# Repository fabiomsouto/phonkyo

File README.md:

# Phonkyo

A PiHat for Onkyo RI-enabled devices, hence the name (PiHat Onkyo).

Phonkyo makes a Raspberry Pi behave like one of Onkyo's own docks. Onkyo receivers have a small RI (Remote
Interactive) jack on the back, which docks use to switch the receiver on and change it to the dock input. Phonkyo speaks
the same protocol, so when you start playing music the receiver comes on and selects DOCK by itself, and after a few
minutes of silence it switches off again.

The music comes from the Pi itself: a PCM5102A DAC on the hat turns it into an AirPlay 2 receiver, a Spotify Connect
device and a headless Plexamp player, feeding the receiver's dock input through a line-level output.

I believe this device could also be used for other RI-enabled devices, such as Marantz, but I have no way to test it
(and therefore implement support)!

## What it does

- **Follows playback.** When something starts playing, the receiver powers on and switches to its DOCK input. When
  playback stops, it switches off again, but only if phonkyo was the one that turned it on.
- **High-quality line output.** PCM5102A DAC, 24-bit/192 kHz, on a 3.5 mm line-out jack meant for an amplifier's
  line input.
- **Onkyo RI control.** A second 3.5 mm jack connects to the receiver's RI port. It sends commands and listens to the
  codes the receiver sends back.
- **The receiver's remote controls Plexamp.** Play/pause, next, previous, fast-forward, rewind and repeat on the
  receiver's own remote work on Plexamp, just as they would on an Onkyo dock. AirPlay and Spotify can't be controlled
  this way; see `install/MANIFEST.md`.
- **Plug-and-play (v0.3).** A HAT ID EEPROM lets the Raspberry Pi recognise the board and load the sound card by itself,
  so there is nothing to add to `config.txt`.

Tested with an Onkyo TX-8020 and a Raspberry Pi Zero 2 W. Selecting the TV input and changing the volume are not
possible over RI on the TX-8020; `install/MANIFEST.md` records the full code search.

## Hardware

| | |
|---|---|
| Form factor | pHAT, 65 x 30 mm, for the Raspberry Pi Zero 2 W (fits any 40-pin Pi) |
| DAC | TI PCM5102A over I2S, own 3.3 V analog regulator |
| Outputs | 3.5 mm line out (J2), 3.5 mm Onkyo RI (J4) |
| RI line | GPIO25, with a series resistor and ESD clamp from v0.3 |
| ID EEPROM | CAT24C256 on ID_SD/ID_SC, write protect by solder jumper (v0.3) |

| Top | Bottom |
|---|---|
|  |  |

The design is in KiCad 10: `phonkyo.kicad_sch` and `phonkyo.kicad_pcb`. **v0.2 is the latest revision that has been built
and tested; v0.3 is designed but not yet built.**

## Buying one

Phonkyo is sold in small, hand-built batches through [obcecado.com/phonkyo](https://obcecado.com/phonkyo/).

- **Basic kit:** an assembled Phonkyo board with the 40-pin header already soldered. €30 plus shipping at the time
  of writing; the product page has the current price.
- **Complete kit:** also includes an audio cable, an RI cable and a 3D-printed case. Not available yet.
- **Shipping** is to European Union countries only.

To order, email [phonkyo@obcecado.com](mailto:phonkyo@obcecado.com?subject=Phonkyo%20order) with:

- the kit you want and how many
- the country it ships to
- your receiver model

I'll reply with the total including shipping and how to pay. There's no online checkout.

RI support varies from receiver to receiver, so check the
[compatibility table](https://obcecado.com/phonkyo/#receiver-compatibility) before ordering. Only the Onkyo TX-8020 has
been tested so far. If yours isn't listed, mention it in your email and I'll tell you what I know.

## Getting started

The software runs on Raspberry Pi OS Lite 64-bit (Trixie) on a Raspberry Pi Zero 2 W. On a fresh install, connect to
the Pi over SSH and run:

```sh
curl -fsSL https://obcecado.com/phonkyo/install.sh | bash
```

It asks which players you want and what to call the device, installs everything, and reboots when it's done. It takes
about 10-15 minutes. Plexamp needs a one-time sign-in code from [plex.tv/claim](https://plex.tv/claim), which it asks
for at the right moment. Running it again is safe, and is how you update. The script is `install/phonkyo-setup.sh`.

The [setup guide](https://obcecado.com/phonkyo/setup/) covers flashing the microSD card and the steps by hand, and
`install/MANIFEST.md` is the full technical record of what gets installed and why:

- the DAC and the ALSA setup
- AirPlay 2 (shairport-sync), Spotify Connect (raspotify) and Plexamp
- the RI control code in `software/phonkyo/` and the `phonkyo-monitor` service that follows playback

## Making boards

`production/v0.3/` has everything needed to order assembled boards from JLCPCB: Gerbers, drill files, and a BOM and
placement file with LCSC part numbers. Its README covers the order settings, the parts, and a bring-up checklist for new
boards. The 40-pin header is soldered by hand, and the ID EEPROM is programmed with `make flash` in `hardware/eeprom/`.

`docs/hardware-review-v0.3.md` is a design review of v0.3: what was found, and what was changed.

## Repository layout

| Path | Contents |
|---|---|
| `phonkyo.kicad_*` | KiCad 10 schematic, PCB and project |
| `production/` | Fabrication files for each revision |
| `hardware/eeprom/` | HAT ID EEPROM image source, device tree overlay, build and flash |
| `software/` | RI control, playback monitor, RI sniffer, board detection, systemd unit |
| `install/MANIFEST.md` | Software setup, measured RI timing and verified RI codes |
| `docs/` | Hardware review |
| `art/` | Board artwork and product renders |
| `3dmodels/` | 3D models missing from the KiCad library |
| `adc/` | PCM5102A datasheet |

## Release notes

### v0.1

Initial release of the Phonkyo project. There is no ID EEPROM present yet, and all the hat exposes is a 3.5mm jack that's
connected to the GPIO pin 25 on the Raspberry Pi. Use a mono or a stereo male-to-male cable to connect your Onkyo remote control to the hat.

### v0.2

This release adds the much acclaimed PCM5102A DAC to the design, allowing to expand the functionality of the device beyond a simple
remote control for your home theater system with RI. Depending on your needs, you will now be able to:
- Control your remote interface home theater to your liking
- Expose the Raspberry Pi as a Spotify device
- Expose the Raspberry Pi as an Airplay device
- Expose the Raspberry Pi as a Plex headless player

### v0.3

This release improves on the board design, particularly around power and ground rails, and removes the SCK jumper, as I don't
predict the need for an external clock source in this particular design. It also:
- Fits the HAT ID EEPROM, so the Raspberry Pi sets the board up by itself
- Adds ESD protection and a series resistor on the RI jack
- Moves the DAC's decoupling capacitors next to its pins, and adds one on the analog supply
- Moves the I2S bit clock onto the top layer, over an unbroken ground plane

## Related projects and documentation

[Macsbug article on PCM5102A](https://macsbug-wordpress-com.translate.goog/2021/02/19/web-radio-of-m5stack-pcm5102a-i2s-dac/)

[TI PCM5102A](https://www.ti.com/lit/ds/symlink/pcm5102a.pdf)

[phatDAC](https://shop.pimoroni.com/products/phat-dac) as inspiration

## License

Phonkyo is licensed under [Creative Commons Attribution-NonCommercial-ShareAlike 4.0 International](LICENSE)
(CC BY-NC-SA 4.0). You may build, modify and share it for non-commercial purposes, as long as you credit the project
and share your changes under the same licence. For commercial use, get in touch.

### Third-party content

These files are not covered by the licence above and remain the property of their owners:

- `adc/pcm5102a.pdf`: the PCM5102A datasheet, © Texas Instruments, included unaltered.
- `3dmodels/Jack_3.5mm_PJ-320D-4A.step`: the 3D model of the Korean Hroparts PJ-320D-4A jack (LCSC C95562), from
  LCSC/EasyEDA, used for the 3D renders only.
- Footprints and symbols from the KiCad libraries, used under the KiCad libraries' licence (CC BY-SA 4.0 with an
  exception for designs that use them).

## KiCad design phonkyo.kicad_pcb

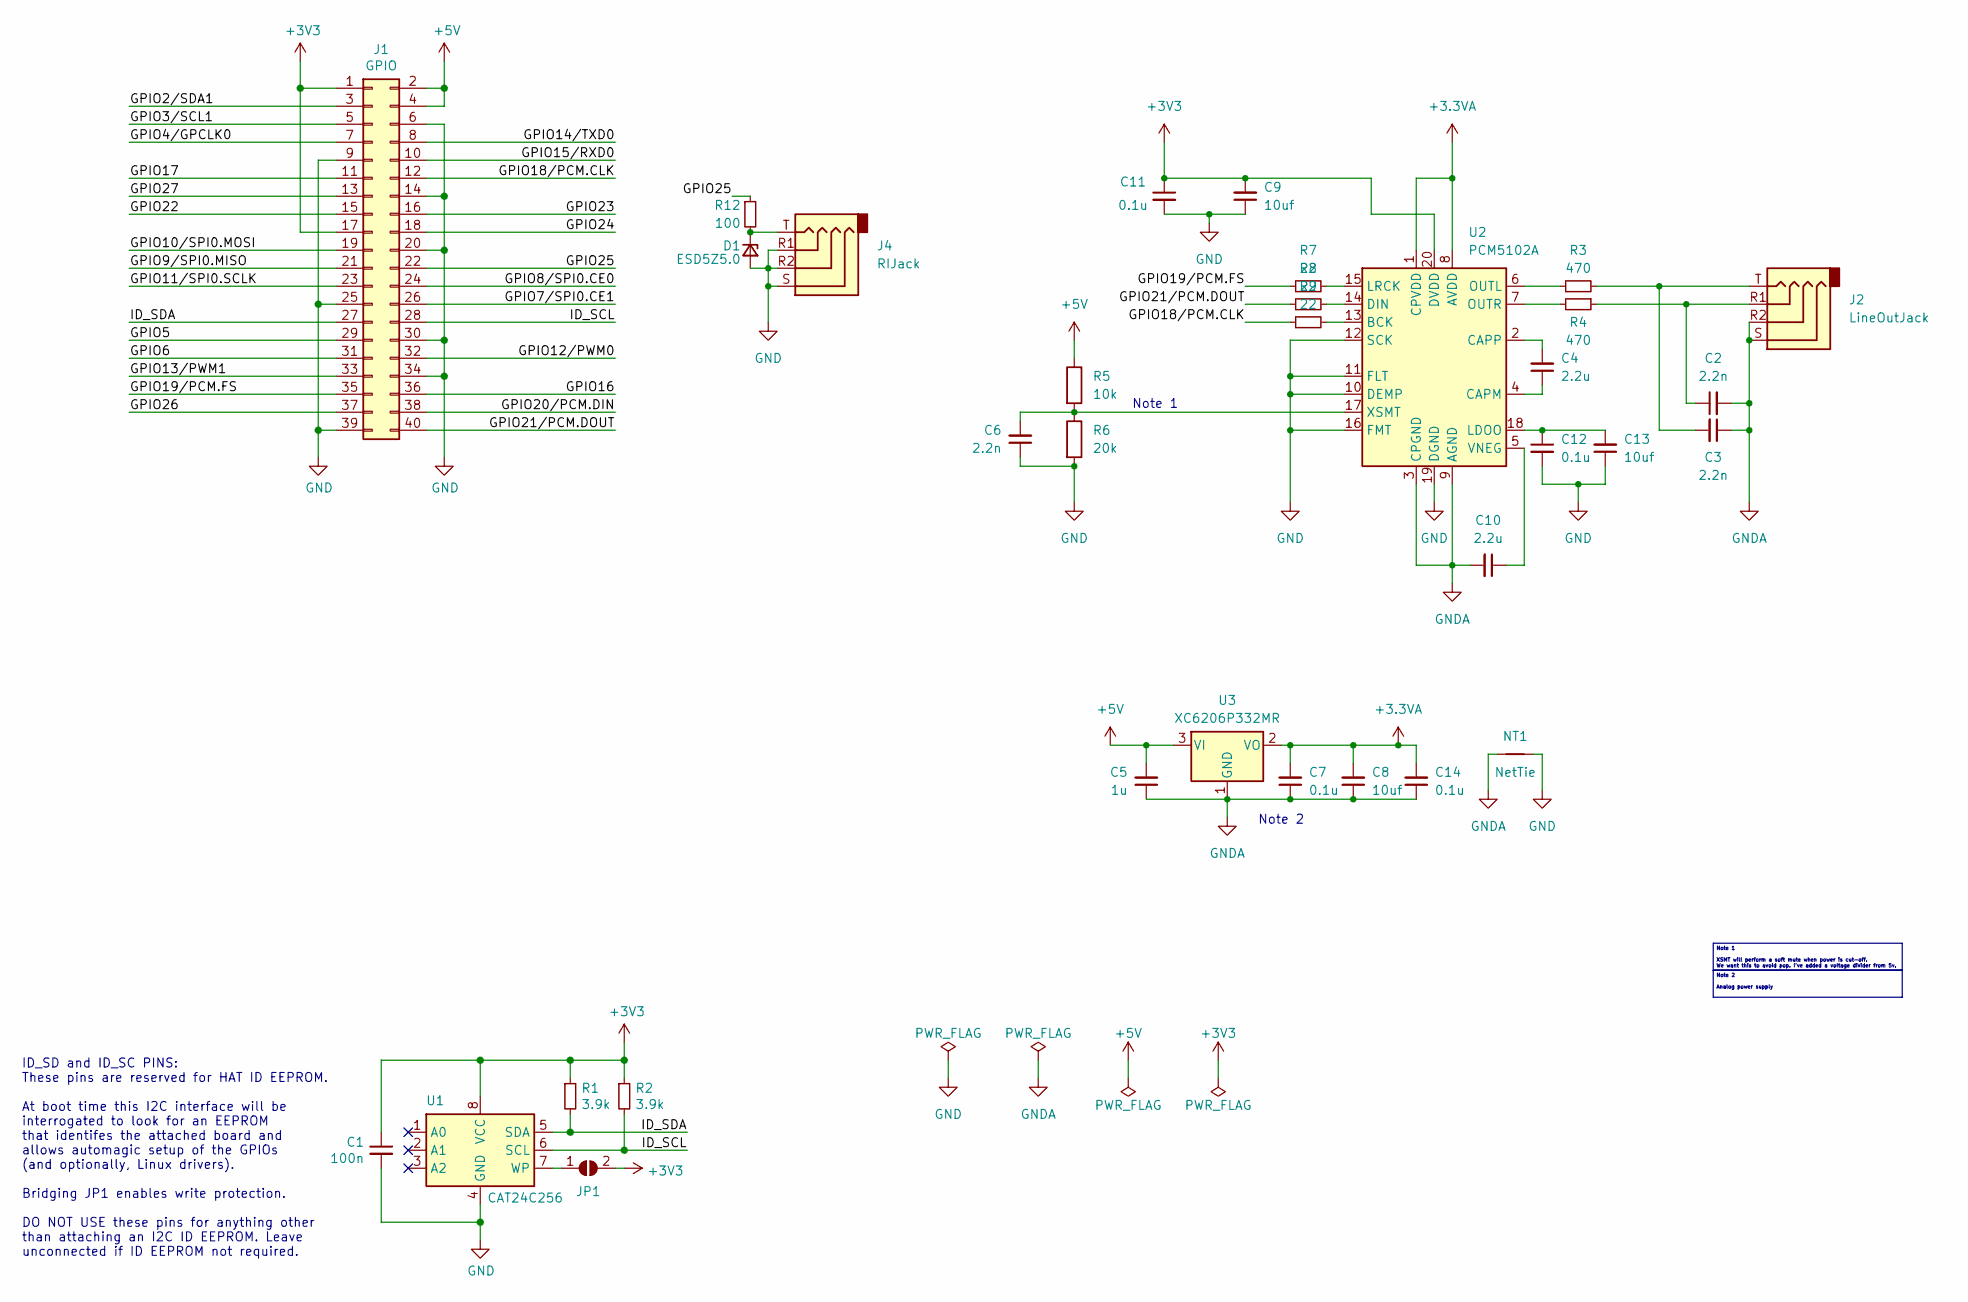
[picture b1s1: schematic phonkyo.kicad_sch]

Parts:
C1: 100n; C_0402_1005Metric; LCSC C1525
C2, C3, C6: 2.2n; C_0402_1005Metric; LCSC C385029
C4, C10: 2.2u; C_0402_1005Metric; LCSC C107369
C5: 1u; C_0603_1608Metric; LCSC C15849
C7: 0.1u; C_0603_1608Metric; LCSC C14663
C8, C9, C13: 10uf; C_0603_1608Metric; LCSC C19702
C11, C12, C14: 0.1u; C_0402_1005Metric; LCSC C1525
D1: ESD5Z5.0; D_SOD-523; LCSC C82044
J1: GPIO; PinSocket_2x20_P2.54mm_Vertical; LCSC C5124634
J2: LineOutJack; Jack_3.5mm_KoreanHropartsElec_PJ-320D-4A_Horizontal; LCSC C95562
J4: RIJack; Jack_3.5mm_KoreanHropartsElec_PJ-320D-4A_Horizontal; LCSC C95562
JP1: ID_WP; SolderJumper-2_P1.3mm_Open_Pad1.0x1.5mm
NT1: NetTie; NetTie-2_SMD_Pad0.5mm
R1, R2: 3.9k; R_0402_1005Metric; LCSC C131467
R3, R4: 470; R_0402_1005Metric; LCSC C25117
R5: 10k; R_0402_1005Metric; LCSC C25744
R6: 20k; R_0402_1005Metric; LCSC C25765
R7, R8, R9: 22; R_0402_1005Metric; LCSC C25092
R12: 100; R_0402_1005Metric; LCSC C25076
U1: CAT24C256; TSSOP-8_4.4x3mm_P0.65mm; LCSC C146734
U2: PCM5102A; TSSOP-20_4.4x6.5mm_P0.65mm; LCSC C107671
U3: XC6206P332MR; SOT-23-3; LCSC C5446

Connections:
+3.3VA: C7.2, C8.2, C14.2, U2.1 (CPVDD), U2.8 (AVDD), U3.2 (VO)
+3V3: C1.1, C9.2, C11.1, J1.1, J1.17, JP1.2 (B), R1.1, R2.1, U1.8 (VCC), U2.20 (DVDD)
+5V: C5.2, J1.2, J1.4, R5.1, U3.3 (VI)
/GPIO2/SDA1: J1.3
/GPIO3/SCL1: J1.5
/GPIO4/GPCLK0: J1.7
/GPIO5: J1.29
/GPIO6: J1.31
/GPIO7/SPI0.CE1: J1.26
/GPIO8/SPI0.CE0: J1.24
/GPIO9/SPI0.MISO: J1.21
/GPIO10/SPI0.MOSI: J1.19
/GPIO11/SPI0.SCLK: J1.23
/GPIO12/PWM0: J1.32
/GPIO13/PWM1: J1.33
/GPIO14/TXD0: J1.8
/GPIO15/RXD0: J1.10
/GPIO16: J1.36
/GPIO17: J1.11
/GPIO18/PCM.CLK: J1.12, R9.1
/GPIO19/PCM.FS: J1.35, R7.1
/GPIO20/PCM.DIN: J1.38
/GPIO21/PCM.DOUT: J1.40, R8.1
/GPIO22: J1.15
/GPIO23: J1.16
/GPIO24: J1.18
/GPIO25: J1.22, R12.1
/GPIO26: J1.37
/GPIO27: J1.13
/ID_SCL: J1.28, R2.2, U1.6 (SCL)
/ID_SDA: J1.27, R1.2, U1.5 (SDA)
GND: C1.2, C6.1, C9.1, C11.2, C12.2, C13.1, D1.2 (A), J1.6, J1.9, J1.14, J1.20, J1.25, J1.30, J1.34, J1.39, J4.R1, J4.R2, J4.S, NT1.2, R6.2, U1.4 (GND), U2.10 (DEMP), U2.11 (FLT), U2.12 (SCK), U2.16 (FMT), U2.19 (DGND)
GNDA: C2.2, C3.1, C5.1, C7.1, C8.1, C10.2, C14.1, J2.R2, J2.S, NT1.1, U2.3 (CPGND), U2.9 (AGND), U3.1 (GND)
unnamed: C2.1, J2.R1, R4.1
unnamed: C3.2, J2.T, R3.2
unnamed: D1.1 (K), J4.T, R12.2
unnamed: JP1.1 (A), U1.7 (WP)
unnamed: R9.2, U2.13 (BCK)
unnamed: C4.1, U2.4 (CAPM)
unnamed: C4.2, U2.2 (CAPP)
unnamed: R8.2, U2.14 (DIN)
unnamed: C12.1, C13.2, U2.18 (LDOO)
unnamed: R7.2, U2.15 (LRCK)
unnamed: R3.1, U2.6 (OUTL)
unnamed: R4.2, U2.7 (OUTR)
unnamed: C10.1, U2.5 (VNEG)
unnamed: C6.2, R5.2, R6.1, U2.17 (XSMT)

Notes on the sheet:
Note 2
ID_SD and ID_SC PINS: These pins are reserved for HAT ID EEPROM. At boot time this I2C interface will be interrogated to look for an EEPROM that identifes the attached board and allows automagic setup of the GPIOs (and optionally, Linux drivers). Bridging JP1 enables write protection. DO NOT USE th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
Note 1
Note 1 XSMT will perform a soft mute when power is cut-off. We want this to avoid pop. I've added a voltage divider from 5v.
Note 2 Analog power supply

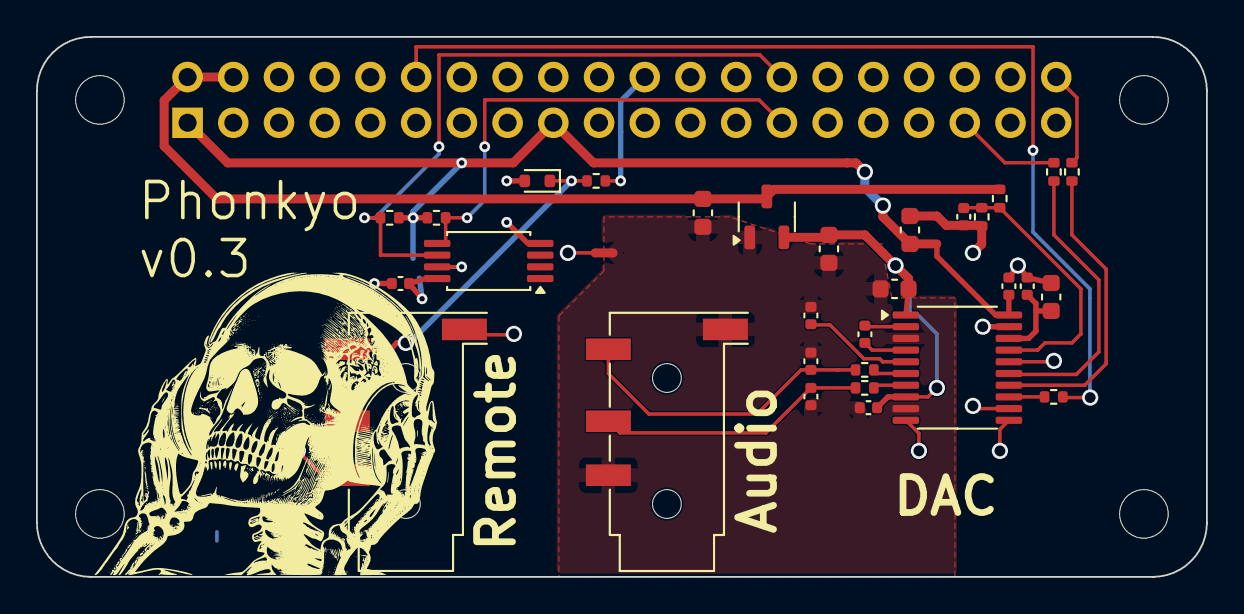
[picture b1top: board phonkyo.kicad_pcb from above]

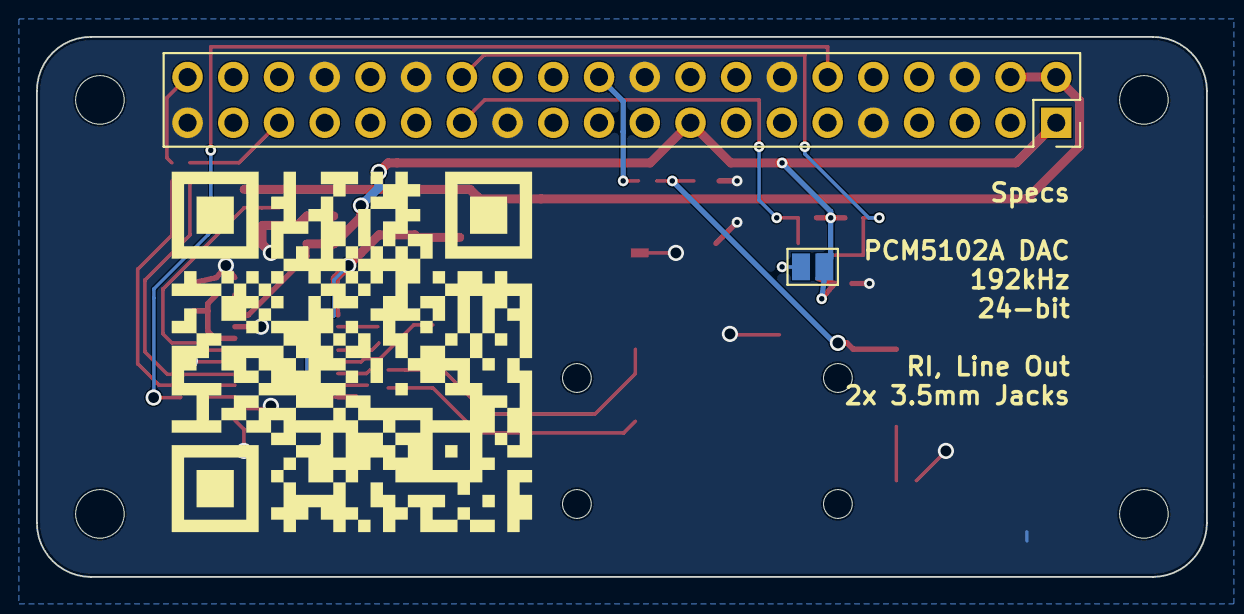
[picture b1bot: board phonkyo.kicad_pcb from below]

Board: 2 copper layers, 65.0 x 30.0 mm, 37 parts (2 on the bottom side), 25 nets.

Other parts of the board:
MH1, MH2, MH3, MH4: MountingHole_2.7mm_M2.5

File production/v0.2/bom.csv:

"Reference","Value","Datasheet","Footprint","Qty","DNP"
"C2,C3,C6","2.2n","~","Capacitor_SMD:C_0402_1005Metric","3",""
"C4,C10","2.2u","~","Capacitor_SMD:C_0402_1005Metric","2",""
"C5","1u","~","Capacitor_SMD:C_0603_1608Metric","1",""
"C7,C11,C12","0.1u","~","Capacitor_SMD:C_0603_1608Metric","3",""
"C8,C9,C13","10uf","~","Capacitor_SMD:C_0603_1608Metric","3",""
"J1","GPIO","","Connector_PinSocket_2.54mm:PinSocket_2x20_P2.54mm_Vertical","1",""
"J2","LineOutJack","~","Connector_Audio:Jack_3.5mm_KoreanHropartsElec_PJ-320D-4A_Horizontal","1",""
"J4","RIJack","~","Connector_Audio:Jack_3.5mm_KoreanHropartsElec_PJ-320D-4A_Horizontal","1",""
"R3,R4","470","~","Resistor_SMD:R_0402_1005Metric","2",""
"R5","10k","~","Resistor_SMD:R_0402_1005Metric","1",""
"R6","20k","~","Resistor_SMD:R_0402_1005Metric","1",""
"R7,R8,R9,R10","22","~","Resistor_SMD:R_0402_1005Metric","4",""
"R11","0","~","Resistor_SMD:R_0402_1005Metric","1",""
"U2","PCM5102A","https://www.ti.com/lit/ds/symlink/pcm5102a.pdf","Package_SO:TSSOP-20_4.4x6.5mm_P0.65mm","1",""
"U3","XC6206P332MR","https://www.torexsemi.com/file/xc6206/XC6206.pdf","Package_TO_SOT_SMD:SOT-23-3","1",""

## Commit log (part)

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2024-10-06 finalize rev2 or v0.2
2024-10-06 finish BOM for v0.2 and submit to production
2024-10-29 add: revision 0.3
